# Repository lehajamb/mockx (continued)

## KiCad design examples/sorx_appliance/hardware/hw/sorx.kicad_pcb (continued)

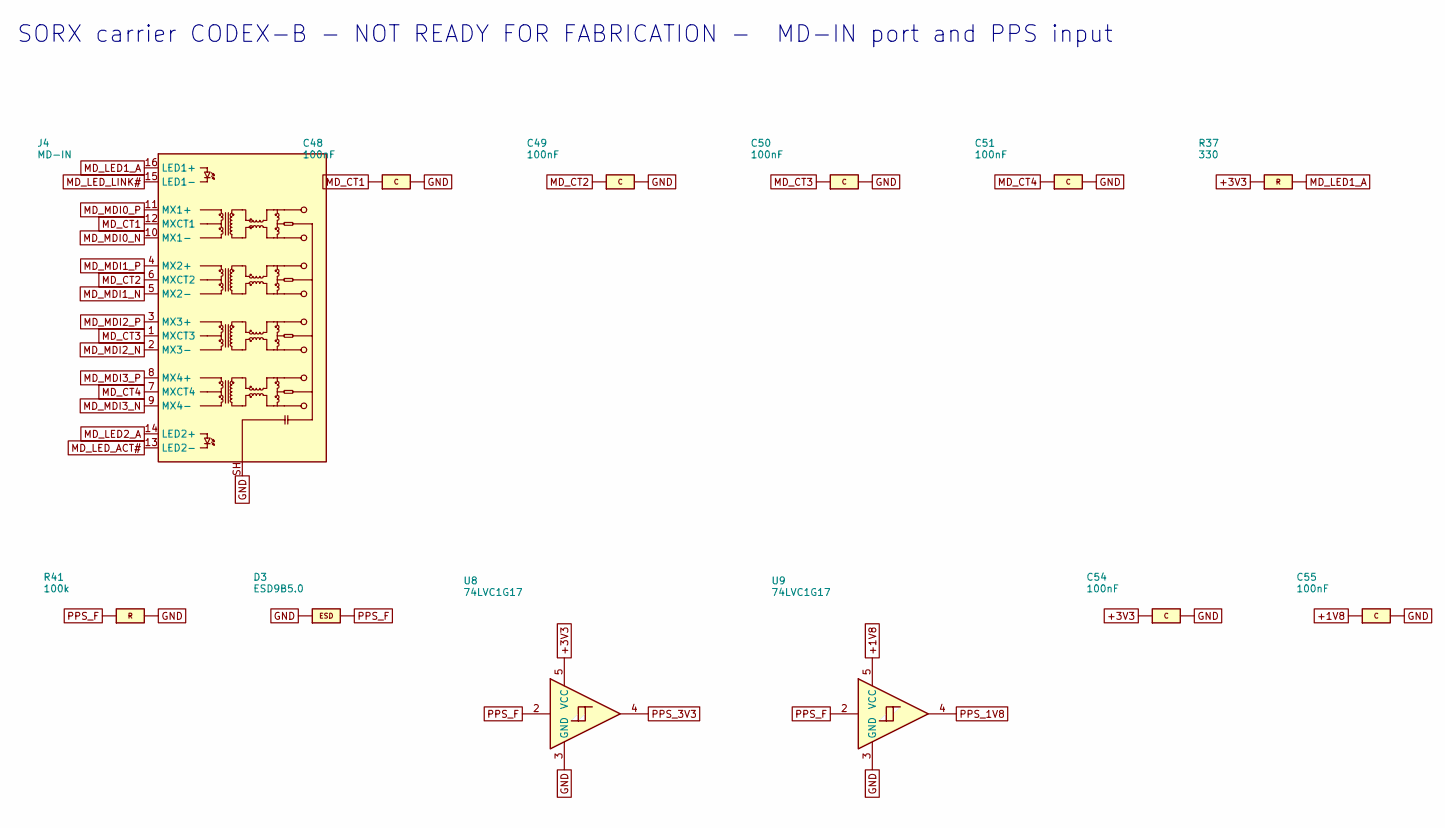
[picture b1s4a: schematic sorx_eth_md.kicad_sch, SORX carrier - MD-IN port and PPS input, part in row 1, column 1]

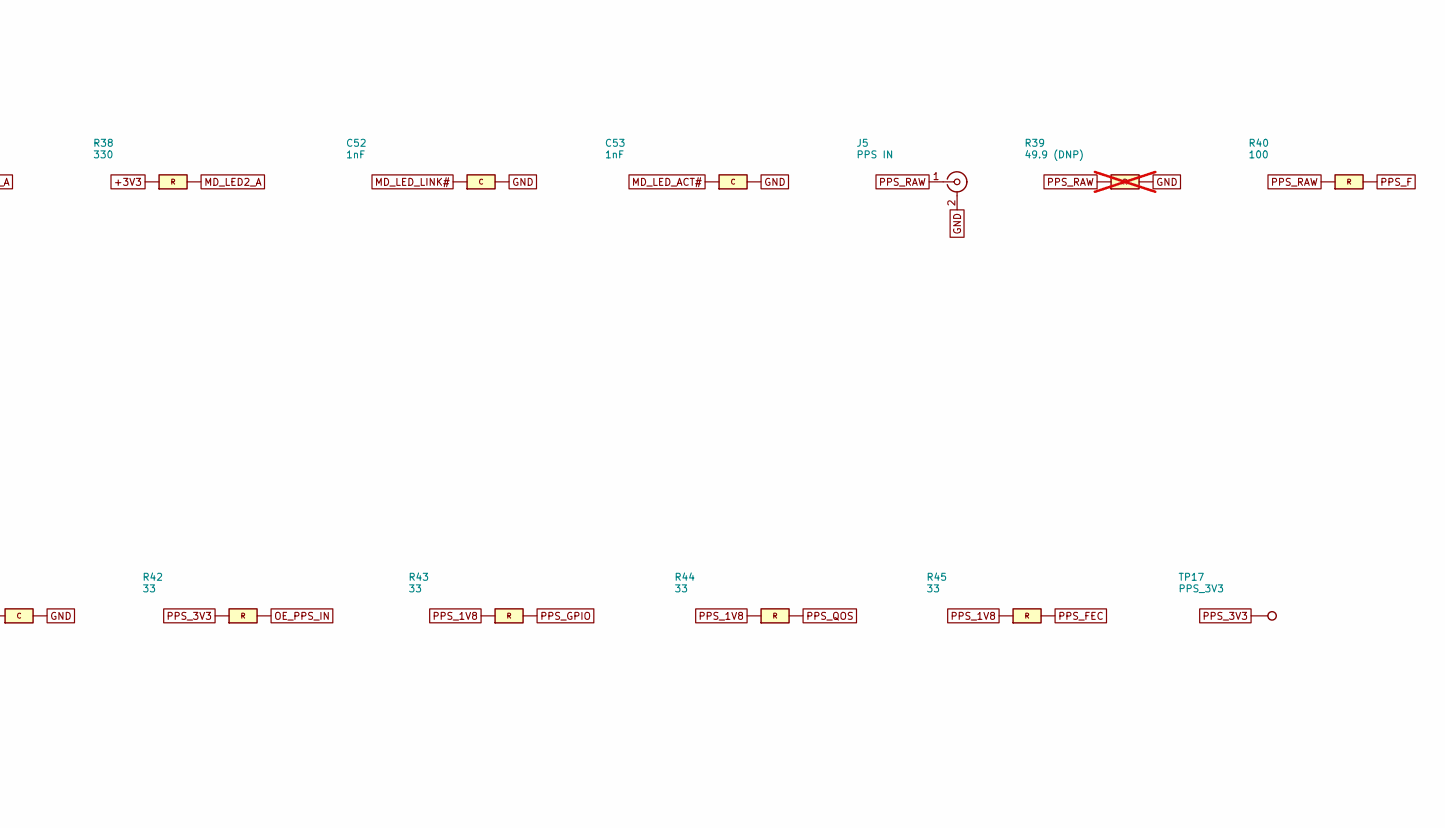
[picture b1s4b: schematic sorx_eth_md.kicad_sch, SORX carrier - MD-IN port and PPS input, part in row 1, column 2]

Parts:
C48, C49, C50, C51, C54, C55: 100nF; C_0402_1005Metric; MPN GRM155R71C104KA88D
C52, C53: 1nF; C_0402_1005Metric; MPN GRM155R71H102KA01D
D3: ESD9B5.0; D_SOD-923; MPN ESD9B5.0ST5G
J4: MD-IN; RJ45_Pulse_JK0654219NL_Horizontal; MPN JK0654219NL
J5: PPS IN; SMA_Amphenol_132289_Drawing; MPN 132289
R37, R38: 330; R_0402_1005Metric; MPN RC0402FR-07330RL
R39: 49.9 (DNP); R_0402_1005Metric; MPN RC0402FR-0749R9L; not fitted
R40: 100; R_0402_1005Metric; MPN RC0402FR-07100RL
R41: 100k; R_0402_1005Metric; MPN RC0402FR-07100KL
R42, R43, R44, R45: 33; R_0402_1005Metric; MPN RC0402FR-0733RL
TP17: PPS_3V3; TestPoint_Pad_D1.0mm
U8, U9: 74LVC1G17; SOT-23-5; MPN SN74LVC1G17DBVR

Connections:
+1V8: C55.1, U9.5 (VCC); also elsewhere on the board
+3V3: C54.1, R37.1, R38.1, U8.5 (VCC); also elsewhere on the board
GND: C48.2, C49.2, C50.2, C51.2, C52.2, C53.2, C54.2, C55.2, D3.2 (A), J4.SH, J5.2 (Ext), R39.2, R41.2, U8.3 (GND), U9.3 (GND); also elsewhere on the board
MD_CT1: C48.1, J4.12 (MXCT1)
MD_CT2: C49.1, J4.6 (MXCT2)
MD_CT3: C50.1, J4.1 (MXCT3)
MD_CT4: C51.1, J4.7 (MXCT4)
MD_LED1_A: J4.16 (LED1+), R37.2
MD_LED2_A: J4.14 (LED2+), R38.2
MD_LED_ACT#: C53.1, J4.13 (LED2-); also elsewhere on the board
MD_LED_LINK#: C52.1, J4.15 (LED1-); also elsewhere on the board
MD_MDI0_N: J4.10 (MX1-); also elsewhere on the board
MD_MDI0_P: J4.11 (MX1+); also elsewhere on the board
MD_MDI1_N: J4.5 (MX2-); also elsewhere on the board
MD_MDI1_P: J4.4 (MX2+); also elsewhere on the board
MD_MDI2_N: J4.2 (MX3-); also elsewhere on the board
MD_MDI2_P: J4.3 (MX3+); also elsewhere on the board
MD_MDI3_N: J4.9 (MX4-); also elsewhere on the board
MD_MDI3_P: J4.8 (MX4+); also elsewhere on the board
OE_PPS_IN: R42.2; also elsewhere on the board
PPS_1V8: R43.1, R44.1, R45.1, U9.4
PPS_3V3: R42.1, TP17.1, U8.4
PPS_F: D3.1 (K), R40.2, R41.1, U8.2, U9.2
PPS_FEC: R45.2; also elsewhere on the board
PPS_GPIO: R43.2; also elsewhere on the board
PPS_QOS: R44.2; also elsewhere on the board
PPS_RAW: J5.1 (In), R39.1, R40.1

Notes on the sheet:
SORX carrier CODEX-B - NOT READY FOR FABRICATION - MD-IN port and PPS input

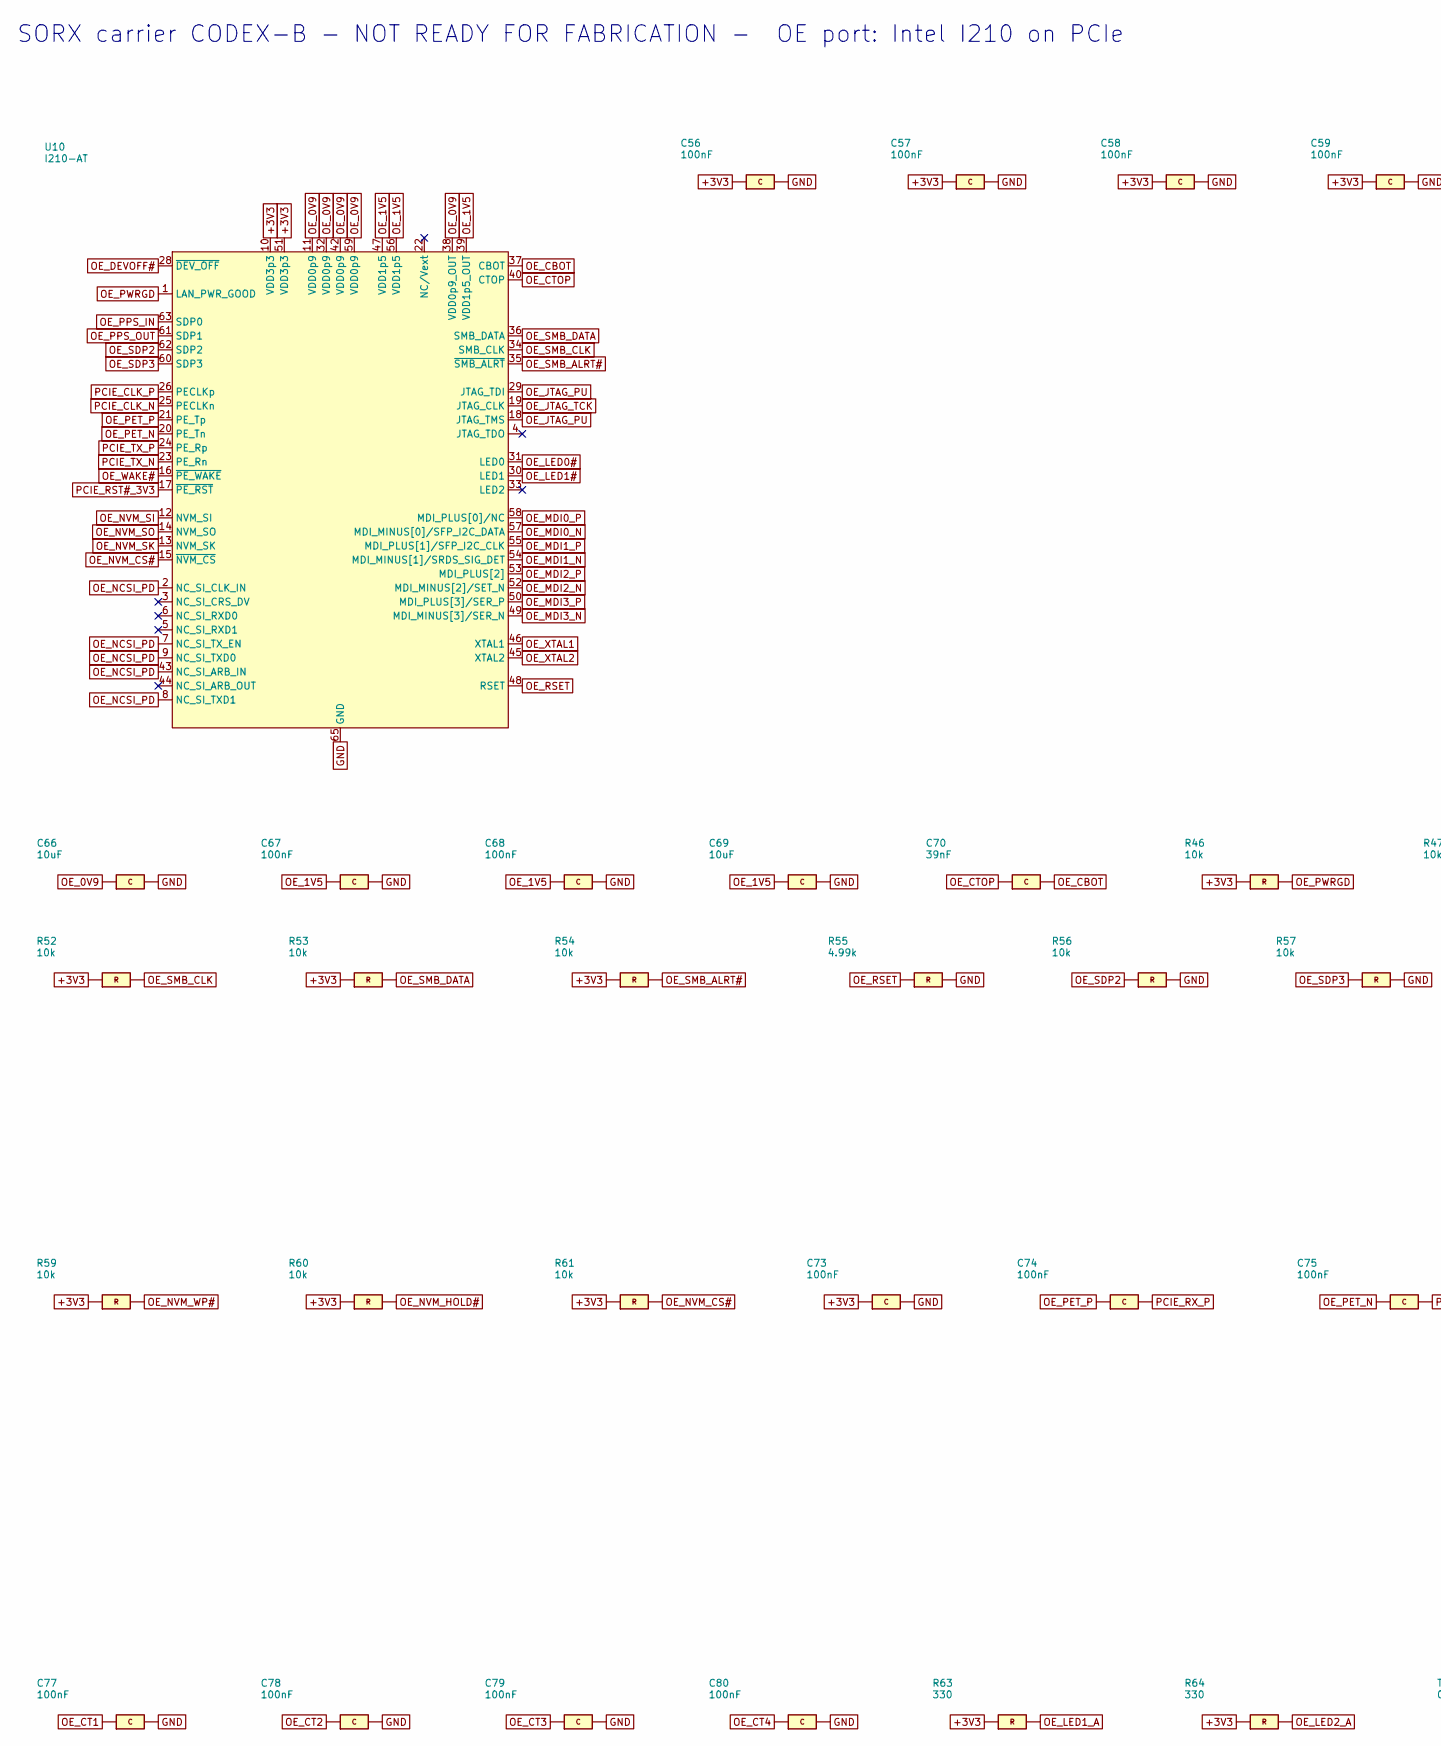
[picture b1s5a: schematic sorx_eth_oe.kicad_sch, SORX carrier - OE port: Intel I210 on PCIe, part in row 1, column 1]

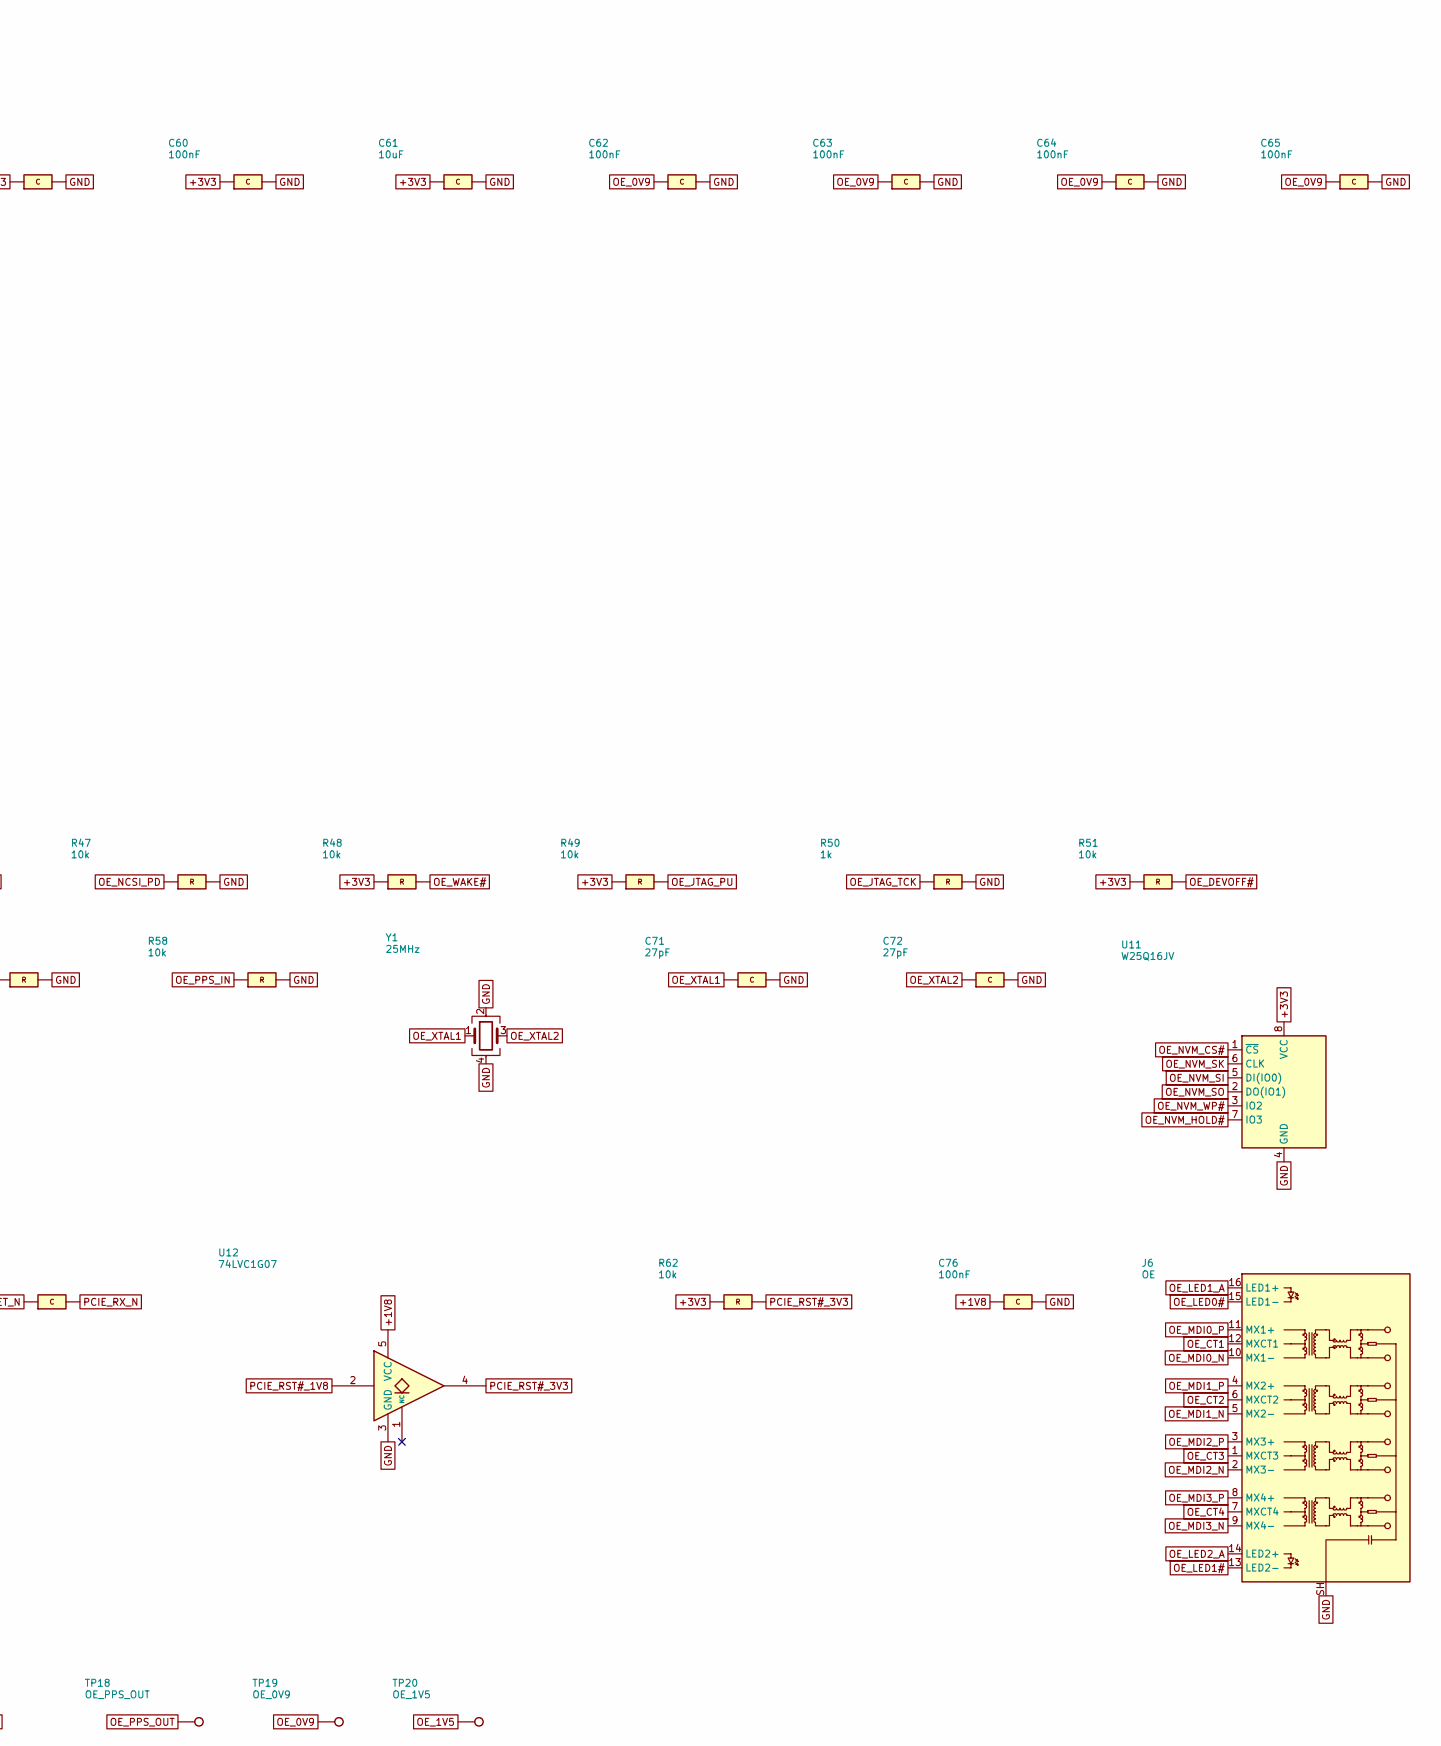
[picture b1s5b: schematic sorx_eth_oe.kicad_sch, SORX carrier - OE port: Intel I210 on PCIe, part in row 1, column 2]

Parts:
C56, C57, C58, C59, C60, C62, C63, C64, C65, C67, C68, C73, C74, C75, C76, C77, C78, C79, C80: 100nF; C_0402_1005Metric; MPN GRM155R71C104KA88D
C61, C66, C69: 10uF; C_0805_2012Metric; MPN GRM21BR61A106KE19L
C70: 39nF; C_0402_1005Metric; MPN GRM155R71E393KA88D
C71, C72: 27pF; C_0402_1005Metric; MPN GRM1555C1H270JA01D
J6: OE; RJ45_Pulse_JK0654219NL_Horizontal; MPN JK0654219NL
R46, R47, R48, R49, R51, R52, R53, R54, R56, R57, R58, R59, R60, R61, R62: 10k; R_0402_1005Metric; MPN RC0402FR-0710KL
R50: 1k; R_0402_1005Metric; MPN RC0402FR-071KL
R55: 4.99k; R_0402_1005Metric; MPN RC0402FR-074K99L
R63, R64: 330; R_0402_1005Metric; MPN RC0402FR-07330RL
TP18: OE_PPS_OUT; TestPoint_Pad_D1.0mm
TP19: OE_0V9; TestPoint_Pad_D1.0mm
TP20: OE_1V5; TestPoint_Pad_D1.0mm
U10: I210-AT; QFN-64-1EP_9x9mm_P0.5mm_EP3.4x3.4mm; MPN WGI210AT S LJXR
U11: W25Q16JV; SOIC-8_5.23x5.23mm_P1.27mm; MPN W25Q16JVSSIQ
U12: 74LVC1G07; SOT-23-5; MPN SN74LVC1G07DBVR
Y1: 25MHz; Crystal_SMD_3225-4Pin_3.2x2.5mm; MPN ABM8-25.000MHZ-B2-T

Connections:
+1V8: C76.1, U12.5 (VCC); also elsewhere on the board
+3V3: C56.1, C57.1, C58.1, C59.1, C60.1, C61.1, C73.1, R46.1, R48.1, R49.1, R51.1, R52.1, R53.1, R54.1, R59.1, R60.1, R61.1, R62.1, R63.1, R64.1, U10.10 (VDD3p3), U10.27 (VDD3p3), U10.41 (VDD3p3), U10.51 (VDD3p3), U10.64 (VDD3p3), U11.8 (VCC); also elsewhere on the board
GND: C56.2, C57.2, C58.2, C59.2, C60.2, C61.2, C62.2, C63.2, C64.2, C65.2, C66.2, C67.2, C68.2, C69.2, C71.2, C72.2, C73.2, C76.2, C77.2, C78.2, C79.2, C80.2, J6.SH, R47.2, R50.2, R55.2, R56.2, R57.2, R58.2, U10.65 (GND), U11.4 (GND), U12.3 (GND), Y1.2, Y1.4; also elsewhere on the board
OE_0V9: C62.1, C63.1, C64.1, C65.1, C66.1, TP19.1, U10.11 (VDD0p9), U10.32 (VDD0p9), U10.38 (VDD0p9_OUT), U10.42 (VDD0p9), U10.59 (VDD0p9)
OE_1V5: C67.1, C68.1, C69.1, TP20.1, U10.39 (VDD1p5_OUT), U10.47 (VDD1p5), U10.56 (VDD1p5)
OE_CBOT: C70.2, U10.37 (CBOT)
OE_CT1: C77.1, J6.12 (MXCT1)
OE_CT2: C78.1, J6.6 (MXCT2)
OE_CT3: C79.1, J6.1 (MXCT3)
OE_CT4: C80.1, J6.7 (MXCT4)
OE_CTOP: C70.1, U10.40 (CTOP)
OE_DEVOFF#: R51.2, U10.28 (~DEV_OFF)
OE_JTAG_PU: R49.2, U10.18 (JTAG_TMS), U10.29 (JTAG_TDI)
OE_JTAG_TCK: R50.1, U10.19 (JTAG_CLK)
OE_LED0#: J6.15 (LED1-), U10.31 (LED0)
OE_LED1#: J6.13 (LED2-), U10.30 (LED1)
OE_LED1_A: J6.16 (LED1+), R63.2
OE_LED2_A: J6.14 (LED2+), R64.2
OE_MDI0_N: J6.10 (MX1-), U10.57 (MDI_MINUS[0]/SFP_I2C_DATA)
OE_MDI0_P: J6.11 (MX1+), U10.58 (MDI_PLUS[0]/NC)
OE_MDI1_N: J6.5 (MX2-), U10.54 (MDI_MINUS[1]/SRDS_SIG_DET)
OE_MDI1_P: J6.4 (MX2+), U10.55 (MDI_PLUS[1]/SFP_I2C_CLK)
OE_MDI2_N: J6.2 (MX3-), U10.52 (MDI_MINUS[2]/SET_N)
OE_MDI2_P: J6.3 (MX3+), U10.53 (MDI_PLUS[2])
OE_MDI3_N: J6.9 (MX4-), U10.49 (MDI_MINUS[3]/SER_N)
OE_MDI3_P: J6.8 (MX4+), U10.50 (MDI_PLUS[3]/SER_P)
OE_NCSI_PD: R47.1, U10.2 (NC_SI_CLK_IN), U10.7 (NC_SI_TX_EN), U10.8 (NC_SI_TXD1), U10.9 (NC_SI_TXD0), U10.43 (NC_SI_ARB_IN)
OE_NVM_CS#: R61.2, U10.15 (~NVM_CS), U11.1 (~CS)
OE_NVM_HOLD#: R60.2, U11.7 (IO3)
OE_NVM_SI: U10.12 (NVM_SI), U11.5 (DI(IO0))
OE_NVM_SK: U10.13 (NVM_SK), U11.6 (CLK)
OE_NVM_SO: U10.14 (NVM_SO), U11.2 (DO(IO1))
OE_NVM_WP#: R59.2, U11.3 (IO2)
OE_PET_N: C75.1, U10.20 (PE_Tn)
OE_PET_P: C74.1, U10.21 (PE_Tp)
OE_PPS_IN: R58.1, U10.63 (SDP0); also elsewhere on the board
OE_PPS_OUT: TP18.1, U10.61 (SDP1)
OE_PWRGD: R46.2, U10.1 (LAN_PWR_GOOD)
OE_RSET: R55.1, U10.48 (RSET)
OE_SDP2: R56.1, U10.62 (SDP2)
OE_SDP3: R57.1, U10.60 (SDP3)
OE_SMB_ALRT#: R54.2, U10.35 (~SMB_ALRT)
OE_SMB_CLK: R52.2, U10.34 (SMB_CLK)
OE_SMB_DATA: R53.2, U10.36 (SMB_DATA)
OE_WAKE#: R48.2, U10.16 (~PE_WAKE)
OE_XTAL1: C71.1, U10.46 (XTAL1), Y1.1
OE_XTAL2: C72.1, U10.45 (XTAL2), Y1.3
PCIE_CLK_N: U10.25 (PECLKn); also elsewhere on the board
PCIE_CLK_P: U10.26 (PECLKp); also elsewhere on the board
PCIE_RST#_1V8: U12.2; also elsewhere on the board
PCIE_RST#_3V3: R62.2, U10.17 (~PE_RST), U12.4
PCIE_RX_N: C75.2; also elsewhere on the board
PCIE_RX_P: C74.2; also elsewhere on the board
PCIE_TX_N: U10.23 (PE_Rn); also elsewhere on the board
PCIE_TX_P: U10.24 (PE_Rp); also elsewhere on the board

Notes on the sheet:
SORX carrier CODEX-B - NOT READY FOR FABRICATION - OE port: Intel I210 on PCIe

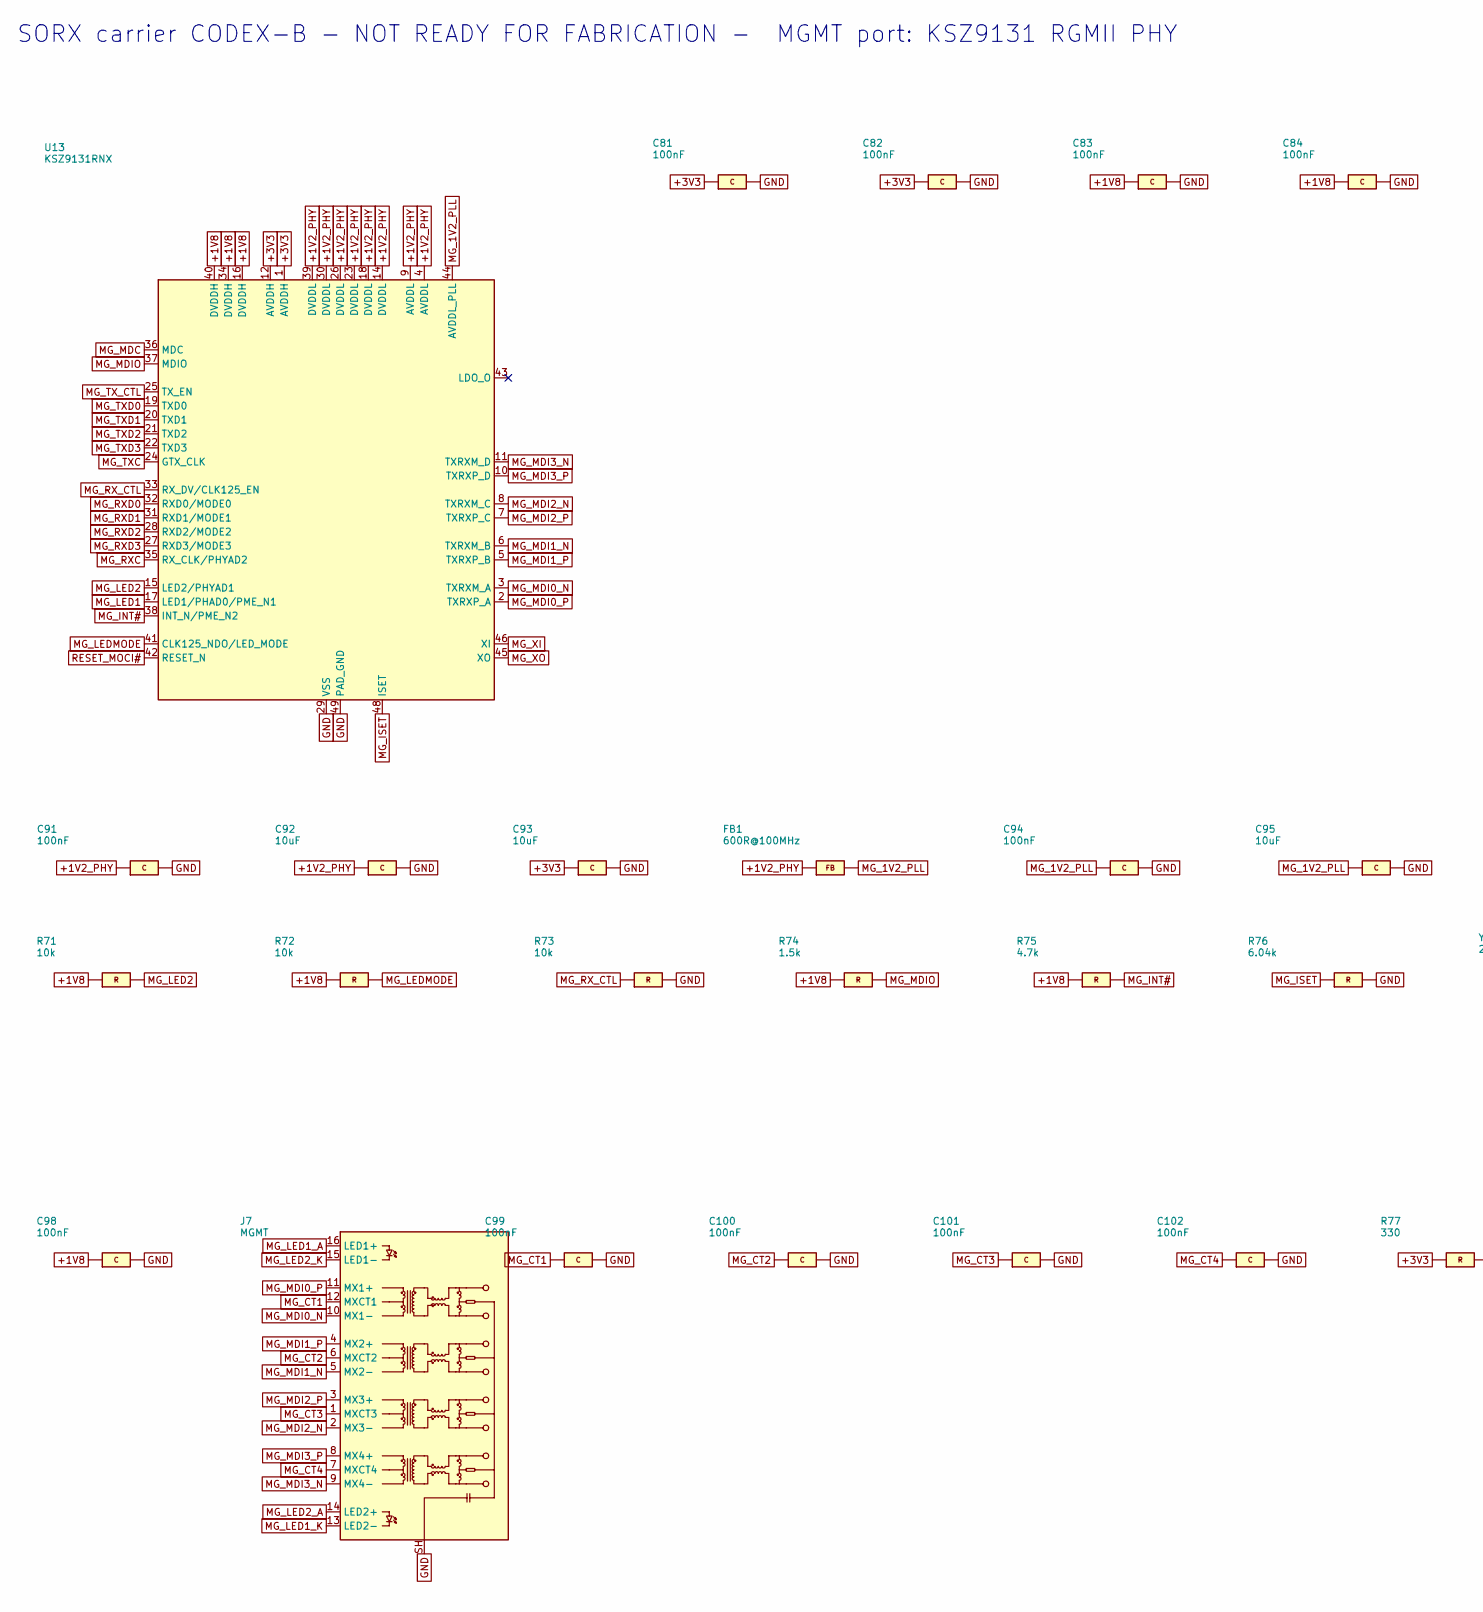
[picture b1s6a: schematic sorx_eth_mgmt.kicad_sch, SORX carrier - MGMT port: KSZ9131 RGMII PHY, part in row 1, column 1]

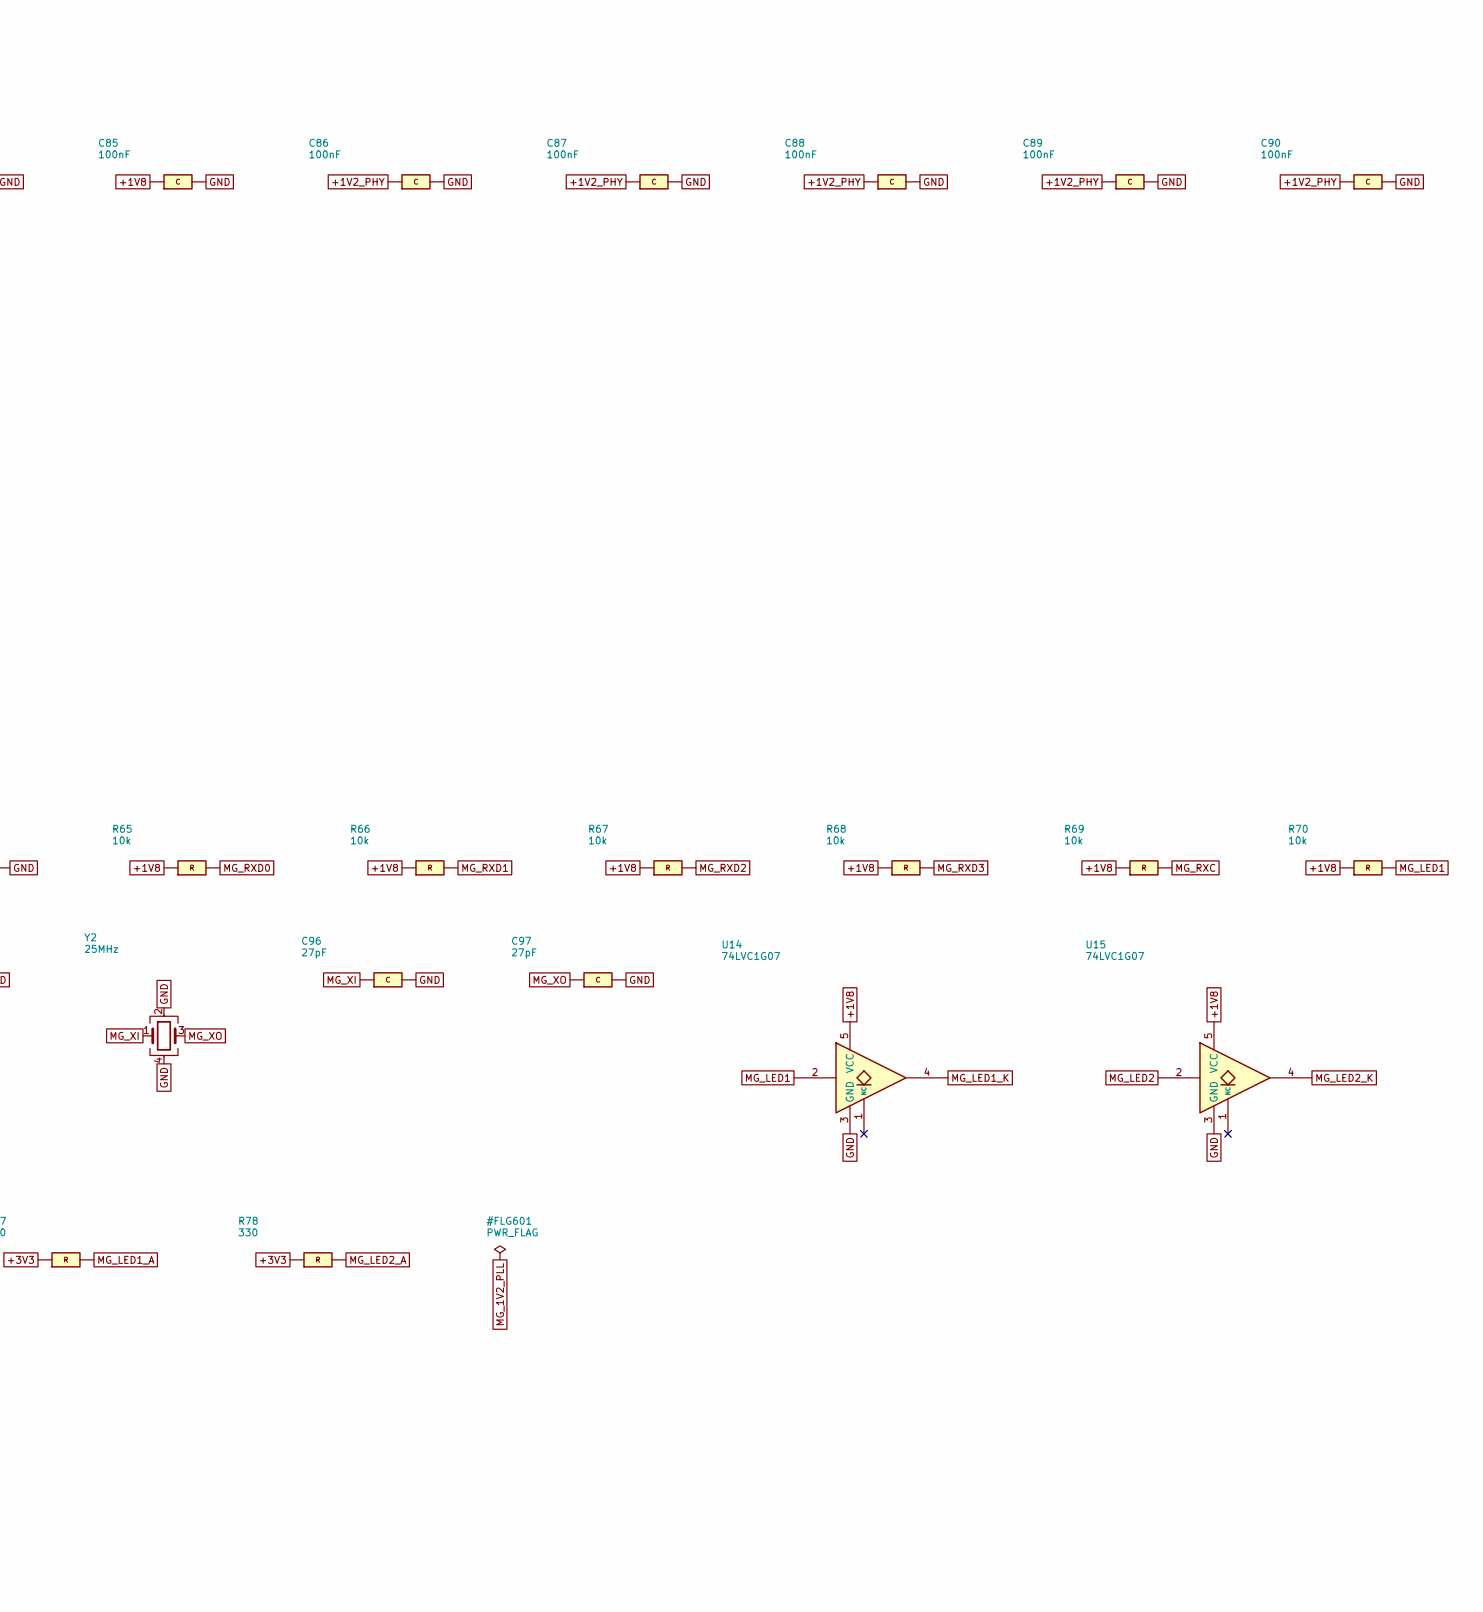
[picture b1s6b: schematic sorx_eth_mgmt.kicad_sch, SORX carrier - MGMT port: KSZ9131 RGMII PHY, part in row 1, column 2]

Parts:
C81, C82, C83, C84, C85, C86, C87, C88, C89, C90, C91, C94, C98, C99, C100, C101, C102: 100nF; C_0402_1005Metric; MPN GRM155R71C104KA88D
C92, C93, C95: 10uF; C_0805_2012Metric; MPN GRM21BR61A106KE19L
C96, C97: 27pF; C_0402_1005Metric; MPN GRM1555C1H270JA01D
FB1: 600R@100MHz; L_0603_1608Metric; MPN BLM18AG601SN1D
J7: MGMT; RJ45_Pulse_JK0654219NL_Horizontal; MPN JK0654219NL
R65, R66, R67, R68, R69, R70, R71, R72, R73: 10k; R_0402_1005Metric; MPN RC0402FR-0710KL
R74: 1.5k; R_0402_1005Metric; MPN RC0402FR-071K5L
R75: 4.7k; R_0402_1005Metric; MPN RC0402FR-074K7L
R76: 6.04k; R_0402_1005Metric; MPN RC0402FR-076K04L
R77, R78: 330; R_0402_1005Metric; MPN RC0402FR-07330RL
U13: KSZ9131RNX; QFN-48-1EP_7x7mm_P0.5mm_EP5.15x5.15mm; MPN KSZ9131RNXI-TR
U14, U15: 74LVC1G07; SOT-23-5; MPN SN74LVC1G07DBVR
Y2: 25MHz; Crystal_SMD_3225-4Pin_3.2x2.5mm; MPN ABM8-25.000MHZ-B2-T

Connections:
+1V2_PHY: C86.1, C87.1, C88.1, C89.1, C90.1, C91.1, C92.1, FB1.1, U13.4 (AVDDL), U13.9 (AVDDL), U13.14 (DVDDL), U13.18 (DVDDL), U13.23 (DVDDL), U13.26 (DVDDL), U13.30 (DVDDL), U13.39 (DVDDL); also elsewhere on the board
+1V8: C83.1, C84.1, C85.1, C98.1, R65.1, R66.1, R67.1, R68.1, R69.1, R70.1, R71.1, R72.1, R74.1, R75.1, U13.16 (DVDDH), U13.34 (DVDDH), U13.40 (DVDDH), U14.5 (VCC), U15.5 (VCC); also elsewhere on the board
+3V3: C81.1, C82.1, C93.1, R77.1, R78.1, U13.1 (AVDDH), U13.12 (AVDDH); also elsewhere on the board
GND: C81.2, C82.2, C83.2, C84.2, C85.2, C86.2, C87.2, C88.2, C89.2, C90.2, C91.2, C92.2, C93.2, C94.2, C95.2, C96.2, C97.2, C98.2, C99.2, C100.2, C101.2, C102.2, J7.SH, R73.2, R76.2, U13.29 (VSS), U13.49 (PAD_GND), U14.3 (GND), U15.3 (GND), Y2.2, Y2.4; also elsewhere on the board
MG_1V2_PLL: C94.1, C95.1, FB1.2, U13.44 (AVDDL_PLL)
MG_CT1: C99.1, J7.12 (MXCT1)
MG_CT2: C100.1, J7.6 (MXCT2)
MG_CT3: C101.1, J7.1 (MXCT3)
MG_CT4: C102.1, J7.7 (MXCT4)
MG_INT#: R75.2, U13.38 (INT_N/PME_N2); also elsewhere on the board
MG_ISET: R76.1, U13.48 (ISET)
MG_LED1: R70.2, U13.17 (LED1/PHAD0/PME_N1), U14.2
MG_LED1_A: J7.16 (LED1+), R77.2
MG_LED1_K: J7.13 (LED2-), U14.4
MG_LED2: R71.2, U13.15 (LED2/PHYAD1), U15.2
MG_LED2_A: J7.14 (LED2+), R78.2
MG_LED2_K: J7.15 (LED1-), U15.4
MG_LEDMODE: R72.2, U13.41 (CLK125_NDO/LED_MODE)
MG_MDC: U13.36 (MDC); also elsewhere on the board
MG_MDI0_N: J7.10 (MX1-), U13.3 (TXRXM_A)
MG_MDI0_P: J7.11 (MX1+), U13.2 (TXRXP_A)
MG_MDI1_N: J7.5 (MX2-), U13.6 (TXRXM_B)
MG_MDI1_P: J7.4 (MX2+), U13.5 (TXRXP_B)
MG_MDI2_N: J7.2 (MX3-), U13.8 (TXRXM_C)
MG_MDI2_P: J7.3 (MX3+), U13.7 (TXRXP_C)
MG_MDI3_N: J7.9 (MX4-), U13.11 (TXRXM_D)
MG_MDI3_P: J7.8 (MX4+), U13.10 (TXRXP_D)
MG_MDIO: R74.2, U13.37 (MDIO); also elsewhere on the board
MG_RXC: R69.2, U13.35 (RX_CLK/PHYAD2); also elsewhere on the board
MG_RXD0: R65.2, U13.32 (RXD0/MODE0); also elsewhere on the board
MG_RXD1: R66.2, U13.31 (RXD1/MODE1); also elsewhere on the board
MG_RXD2: R67.2, U13.28 (RXD2/MODE2); also elsewhere on the board
MG_RXD3: R68.2, U13.27 (RXD3/MODE3); also elsewhere on the board
MG_RX_CTL: R73.1, U13.33 (RX_DV/CLK125_EN); also elsewhere on the board
MG_TXC: U13.24 (GTX_CLK); also elsewhere on the board
MG_TXD0: U13.19 (TXD0); also elsewhere on the board
MG_TXD1: U13.20 (TXD1); also elsewhere on the board
MG_TXD2: U13.21 (TXD2); also elsewhere on the board
MG_TXD3: U13.22 (TXD3); also elsewhere on the board
MG_TX_CTL: U13.25 (TX_EN); also elsewhere on the board
MG_XI: C96.1, U13.46 (XI), Y2.1
MG_XO: C97.1, U13.45 (XO), Y2.3
RESET_MOCI#: U13.42 (RESET_N); also elsewhere on the board

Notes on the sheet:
SORX carrier CODEX-B - NOT READY FOR FABRICATION - MGMT port: KSZ9131 RGMII PHY
